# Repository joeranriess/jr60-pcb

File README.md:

# jr60-pcb
 My first 60% keyboard pcb design

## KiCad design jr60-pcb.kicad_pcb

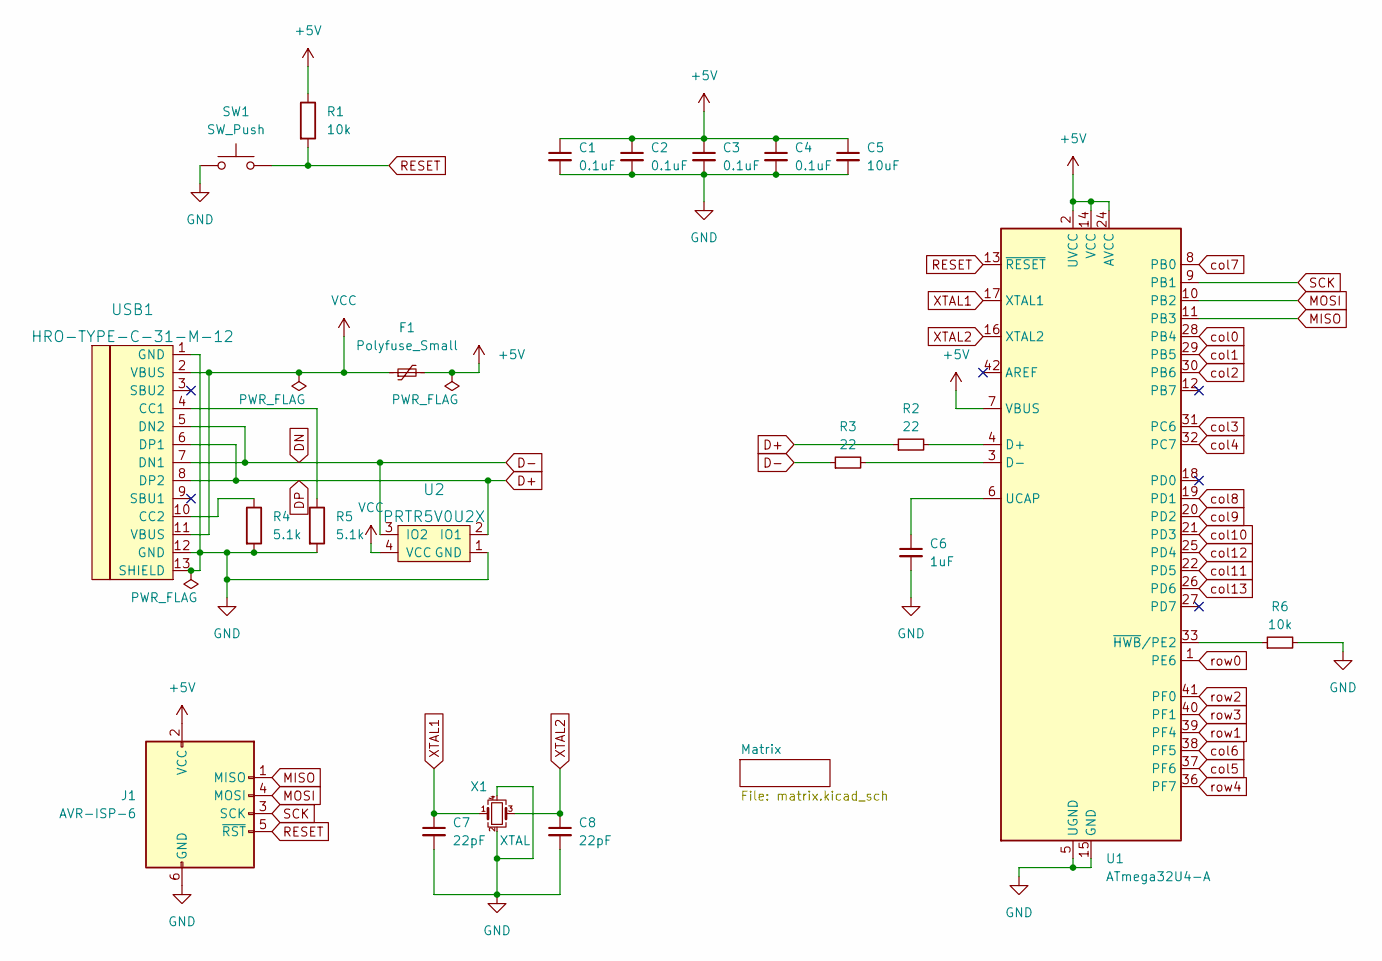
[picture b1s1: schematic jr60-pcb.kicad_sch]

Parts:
C1, C2, C3, C4: 0.1uF; C_0805_2012Metric_Pad1.18x1.45mm_HandSolder
C5: 10uF; C_0805_2012Metric_Pad1.18x1.45mm_HandSolder
C6: 1uF; C_0805_2012Metric_Pad1.18x1.45mm_HandSolder
C7, C8: 22pF; C_0805_2012Metric_Pad1.18x1.45mm_HandSolder
F1: Polyfuse_Small; Fuse_1206_3216Metric_Pad1.42x1.75mm_HandSolder
J1: AVR-ISP-6; Reset_Pretty-Mask
R1, R6: 10k; R_0805_2012Metric_Pad1.20x1.40mm_HandSolder
R2, R3: 22; R_0805_2012Metric_Pad1.20x1.40mm_HandSolder
R4, R5: 5.1k; R_0805_2012Metric_Pad1.20x1.40mm_HandSolder
SW1: SW_Push; SW_SPST_TL3342
U1: ATmega32U4-A; TQFP-44_10x10mm_P0.8mm
U2: PRTR5V0U2X; SOT143B
USB1: HRO-TYPE-C-31-M-12; HRO-TYPE-C-31-M-12-HandSoldering
X1: XTAL; Crystal_SMD_3225-4Pin_3.2x2.5mm_HandSoldering

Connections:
+5V: C1.1, C2.1, C3.1, C4.1, C5.1, F1.2, J1.2 (VCC), R1.1, U1.2 (UVCC), U1.7 (VBUS), U1.14 (VCC), U1.24 (AVCC), U1.34 (VCC), U1.44 (AVCC)
D+: R2.1, U2.2 (IO1), USB1.6 (DP1), USB1.8 (DP2)
D-: R3.1, U2.3 (IO2), USB1.5 (DN2), USB1.7 (DN1)
GND: C1.2, C2.2, C3.2, C4.2, C5.2, C6.2, C7.2, C8.2, J1.6 (GND), R4.2, R5.2, R6.2, SW1.1, U1.5 (UGND), U1.15 (GND), U1.23 (GND), U1.35 (GND), U1.43 (GND), U2.1 (GND), USB1.1 (GND), USB1.12 (GND), USB1.13 (SHIELD), X1.2, X1.4
MISO: J1.1 (MISO), U1.11 (PB3)
MOSI: J1.4 (MOSI), U1.10 (PB2)
unnamed: C6.1, U1.6 (UCAP)
unnamed: R2.2, U1.4 (D+)
unnamed: R3.2, U1.3 (D-)
unnamed: R4.1, USB1.10 (CC2)
unnamed: R5.1, USB1.4 (CC1)
unnamed: R6.1, U1.33 (~HWB/PE2)
RESET: J1.5 (~RST), R1.2, SW1.2, U1.13 (~RESET)
SCK: J1.3 (SCK), U1.9 (PB1)
VCC: F1.1, U2.4 (VCC), USB1.2 (VBUS), USB1.11 (VBUS)
XTAL1: C7.1, U1.17 (XTAL1), X1.1
XTAL2: C8.1, U1.16 (XTAL2), X1.3
col0: U1.28 (PB4); also elsewhere on the board
col1: U1.29 (PB5); also elsewhere on the board
col2: U1.30 (PB6); also elsewhere on the board
col3: U1.31 (PC6); also elsewhere on the board
col4: U1.32 (PC7); also elsewhere on the board
col5: U1.37 (PF6); also elsewhere on the board
col6: U1.38 (PF5); also elsewhere on the board
col7: U1.8 (PB0); also elsewhere on the board
col8: U1.19 (PD1); also elsewhere on the board
col9: U1.20 (PD2); also elsewhere on the board
col10: U1.21 (PD3); also elsewhere on the board
col11: U1.22 (PD5); also elsewhere on the board
col12: U1.25 (PD4); also elsewhere on the board
col13: U1.26 (PD6); also elsewhere on the board
row0: U1.1 (PE6); also elsewhere on the board
row1: U1.39 (PF4); also elsewhere on the board
row2: U1.41 (PF0); also elsewhere on the board
row3: U1.40 (PF1); also elsewhere on the board
row4: U1.36 (PF7); also elsewhere on the board

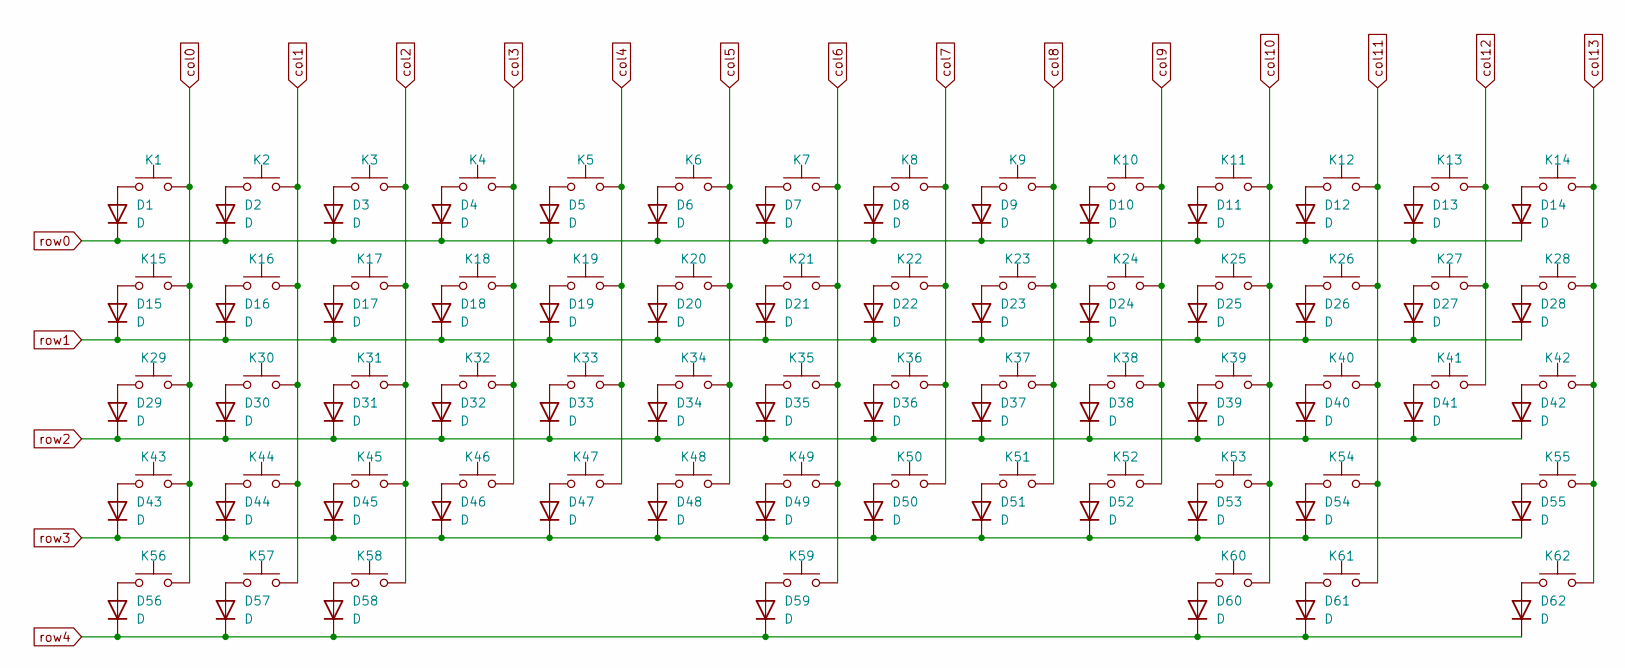
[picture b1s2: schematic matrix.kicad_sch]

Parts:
D1, D2, D3, D4, D5, D6, D7, D8, D9, D10, D11, D12, D13, D14, D15, D16, D17, D18, D19, D20, D21, D22, D23, D24, D25, D26, D27, D28, D29, D30, D31, D32, D33, D34, D35, D36, D37, D38, D39, D40, D41, D42, D43, D44, D45, D46, D47, D48, D49, D50, D51, D52, D53, D54, D55, D56, D57, D58, D59, D60, D61, D62: D; D_SOD-123
K1: ESC; MX-1U
K2: #1; MX-1U
K3: #2; MX-1U
K4: #3; MX-1U
K5: #4; MX-1U
K6: #5; MX-1U
K7: #6; MX-1U
K8: #7; MX-1U
K9: #8; MX-1U
K10: #9; MX-1U
K11: #0; MX-1U
K12: -_; MX-1U
K13: =+; MX-1U
K14: \|; MX-1U
K15: TAB; MX-1.5U
K16: Q; MX-1U
K17: W; MX-1U
K18: E; MX-1U
K19: R; MX-1U
K20: T; MX-1U
K21: Y; MX-1U
K22: U; MX-1U
K23: I; MX-1U
K24: O; MX-1U
K25: P; MX-1U
K26: [{; MX-1U
K27: ]}; MX-1U
K28: BSPC; MX-1.5U
K29: CPLK; MX-1.75U
K30: A; MX-1U
K31: S; MX-1U
K32: D; MX-1U
K33: F; MX-1U
K34: G; MX-1U
K35: H; MX-1U
K36: J; MX-1U
K37: K; MX-1U
K38: L; MX-1U
K39: ;:; MX-1U
K40: '"; MX-1U
K41: DEL; MX-1U
K42: ENTER; MX-2.25U
K43: LSHIFT; MX-2.25U
K44: Z; MX-1U
K45: X; MX-1U
K46: C; MX-1U
K47: V; MX-1U
K48: B; MX-1U
K49: N; MX-1U
K50: M; MX-1U
K51: ,<; MX-1U
K52: .>; MX-1U
K53: /?; MX-1U
K54: RSHIFT; MX-1.75U
K55: FN1; MX-1U
K56: LCTRL; MX-1.5U
K57: LWIN; MX-1U
K58: LALT; MX-1.5U
K59: SPACE; MX-7U-ReversedStabilizers
K60: RALT; MX-1.5U
K61: RWIN; MX-1U
K62: RCTRL; MX-1.5U

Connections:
unnamed: D1.1 (A), K1.1
unnamed: D2.1 (A), K2.1
unnamed: D3.1 (A), K3.1
unnamed: D4.1 (A), K4.1
unnamed: D5.1 (A), K5.1
unnamed: D6.1 (A), K6.1
unnamed: D7.1 (A), K7.1
unnamed: D8.1 (A), K8.1
unnamed: D9.1 (A), K9.1
unnamed: D10.1 (A), K10.1
unnamed: D11.1 (A), K11.1
unnamed: D12.1 (A), K12.1
unnamed: D13.1 (A), K13.1
unnamed: D14.1 (A), K14.1
unnamed: D15.1 (A), K15.1
unnamed: D16.1 (A), K16.1
unnamed: D17.1 (A), K17.1
unnamed: D18.1 (A), K18.1
unnamed: D19.1 (A), K19.1
unnamed: D20.1 (A), K20.1
unnamed: D21.1 (A), K21.1
unnamed: D22.1 (A), K22.1
unnamed: D23.1 (A), K23.1
unnamed: D24.1 (A), K24.1
unnamed: D25.1 (A), K25.1
unnamed: D26.1 (A), K26.1
unnamed: D27.1 (A), K27.1
unnamed: D28.1 (A), K28.1
unnamed: D29.1 (A), K29.1
unnamed: D30.1 (A), K30.1
unnamed: D31.1 (A), K31.1
unnamed: D32.1 (A), K32.1
unnamed: D33.1 (A), K33.1
unnamed: D34.1 (A), K34.1
unnamed: D35.1 (A), K35.1
unnamed: D36.1 (A), K36.1
unnamed: D37.1 (A), K37.1
unnamed: D38.1 (A), K38.1
unnamed: D39.1 (A), K39.1
unnamed: D40.1 (A), K40.1
unnamed: D41.1 (A), K41.1
unnamed: D42.1 (A), K42.1
unnamed: D43.1 (A), K43.1
unnamed: D44.1 (A), K44.1
unnamed: D45.1 (A), K45.1
unnamed: D46.1 (A), K46.1
unnamed: D47.1 (A), K47.1
unnamed: D48.1 (A), K48.1
unnamed: D49.1 (A), K49.1
unnamed: D50.1 (A), K50.1
unnamed: D51.1 (A), K51.1
unnamed: D52.1 (A), K52.1
unnamed: D53.1 (A), K53.1
unnamed: D54.1 (A), K54.1
unnamed: D55.1 (A), K55.1
unnamed: D56.1 (A), K56.1
unnamed: D57.1 (A), K57.1
unnamed: D58.1 (A), K58.1
unnamed: D59.1 (A), K59.1
unnamed: D60.1 (A), K60.1
unnamed: D61.1 (A), K61.1
unnamed: D62.1 (A), K62.1
col0: K1.2, K15.2, K29.2, K43.2, K56.2; also elsewhere on the board
col1: K2.2, K16.2, K30.2, K44.2, K57.2; also elsewhere on the board
col2: K3.2, K17.2, K31.2, K45.2, K58.2; also elsewhere on the board
col3: K4.2, K18.2, K32.2, K46.2; also elsewhere on the board
col4: K5.2, K19.2, K33.2, K47.2; also elsewhere on the board
col5: K6.2, K20.2, K34.2, K48.2; also elsewhere on the board
col6: K7.2, K21.2, K35.2, K49.2, K59.2; also elsewhere on the board
col7: K8.2, K22.2, K36.2, K50.2; also elsewhere on the board
col8: K9.2, K23.2, K37.2, K51.2; also elsewhere on the board
col9: K10.2, K24.2, K38.2, K52.2; also elsewhere on the board
col10: K11.2, K25.2, K39.2, K53.2, K60.2; also elsewhere on the board
col11: K12.2, K26.2, K40.2, K54.2, K61.2; also elsewhere on the board
col12: K13.2, K27.2, K41.2; also elsewhere on the board
col13: K14.2, K28.2, K42.2, K55.2, K62.2; also elsewhere on the board
row0: D1.2 (K), D2.2 (K), D3.2 (K), D4.2 (K), D5.2 (K), D6.2 (K), D7.2 (K), D8.2 (K), D9.2 (K), D10.2 (K), D11.2 (K), D12.2 (K), D13.2 (K), D14.2 (K); also elsewhere on the board
row1: D15.2 (K), D16.2 (K), D17.2 (K), D18.2 (K), D19.2 (K), D20.2 (K), D21.2 (K), D22.2 (K), D23.2 (K), D24.2 (K), D25.2 (K), D26.2 (K), D27.2 (K), D28.2 (K); also elsewhere on the board
row2: D29.2 (K), D30.2 (K), D31.2 (K), D32.2 (K), D33.2 (K), D34.2 (K), D35.2 (K), D36.2 (K), D37.2 (K), D38.2 (K), D39.2 (K), D40.2 (K), D41.2 (K), D42.2 (K); also elsewhere on the board
row3: D43.2 (K), D44.2 (K), D45.2 (K), D46.2 (K), D47.2 (K), D48.2 (K), D49.2 (K), D50.2 (K), D51.2 (K), D52.2 (K), D53.2 (K), D54.2 (K), D55.2 (K); also elsewhere on the board
row4: D56.2 (K), D57.2 (K), D58.2 (K), D59.2 (K), D60.2 (K), D61.2 (K), D62.2 (K); also elsewhere on the board

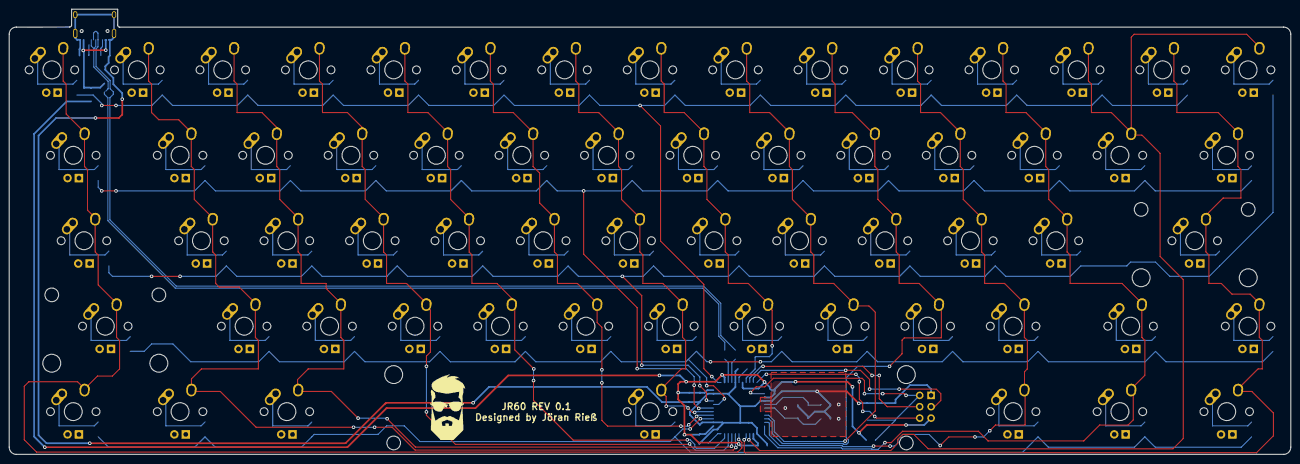
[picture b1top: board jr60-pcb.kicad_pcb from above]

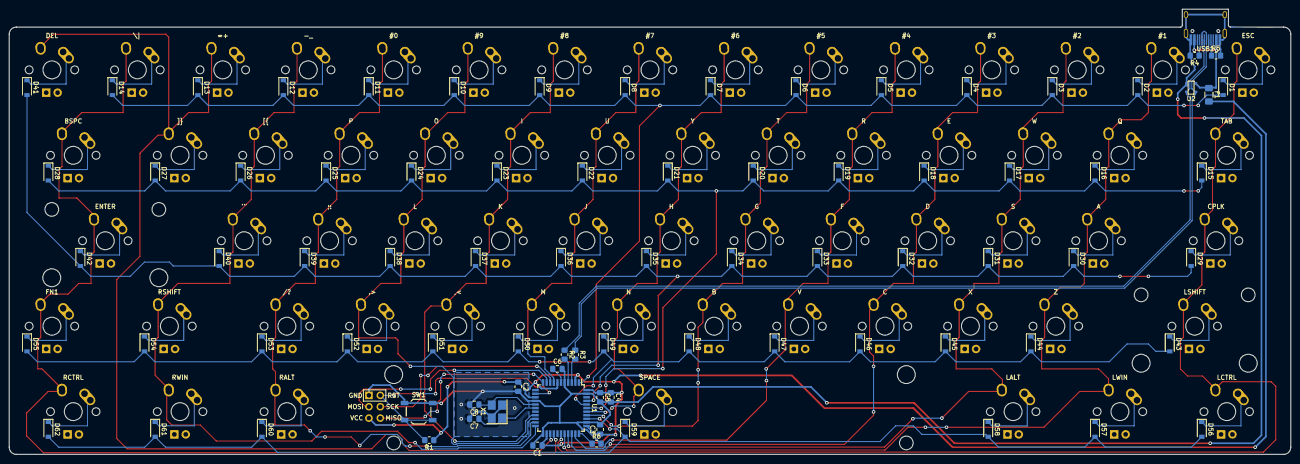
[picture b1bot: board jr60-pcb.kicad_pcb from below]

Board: 2 copper layers, 285.8 x 99.3 mm, 145 parts (83 on the bottom side), 98 nets.

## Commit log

2022-11-06 First commit
    with kicad project file
2022-11-06 Add submodules
2022-11-06 Add footprint libraries
2022-11-06 Add submodules type c
2022-11-06 add type c footprint
2022-11-06 Base schema done
2022-11-06 started matrix
2022-11-28 Added keys
2022-11-28 small adjustment
2022-12-17 finished schematic
2022-12-17 added power flags
2022-12-17 added footprints
2022-12-17 created pcb w/o traces
2022-12-17 started column tracing
2022-12-17 whatever they want
2022-12-18 added all traces
2022-12-18 changed label visibility
2022-12-18 close to finish - at least I think
2022-12-29 pre final
